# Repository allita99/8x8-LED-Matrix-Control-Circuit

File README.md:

# 8×8 LED Matrix Control Shield

This repository contains the hardware design files for an 8×8 LED matrix controller capable of driving 64 LEDs at 15 V. The design was created using KiCad and includes all necessary files for review, modification, and fabrication.

---

## Overview

- 8×8 LED matrix control (64 LEDs)
- Designed for 15 V LED operation
- Fully custom PCB layout
- Suitable for applications such as visual interfaces, experimental setups, or embedded systems

---

## Repository Contents

- **KiCad Project Files**  
  Schematic and PCB layout files for editing and further development.

- **Gerber Files**  
  Ready-to-manufacture files for PCB fabrication.

- **Images**  
  Rendered views and design previews of the board and schematics.

---

## PCB Render (Assembled View)

---

## Schematic

---

## PCB Layout

### Top Layer

### Bottom Layer

---

## Getting Started

1. Clone the repository:
   ```bash
   git clone <your-repo-url>

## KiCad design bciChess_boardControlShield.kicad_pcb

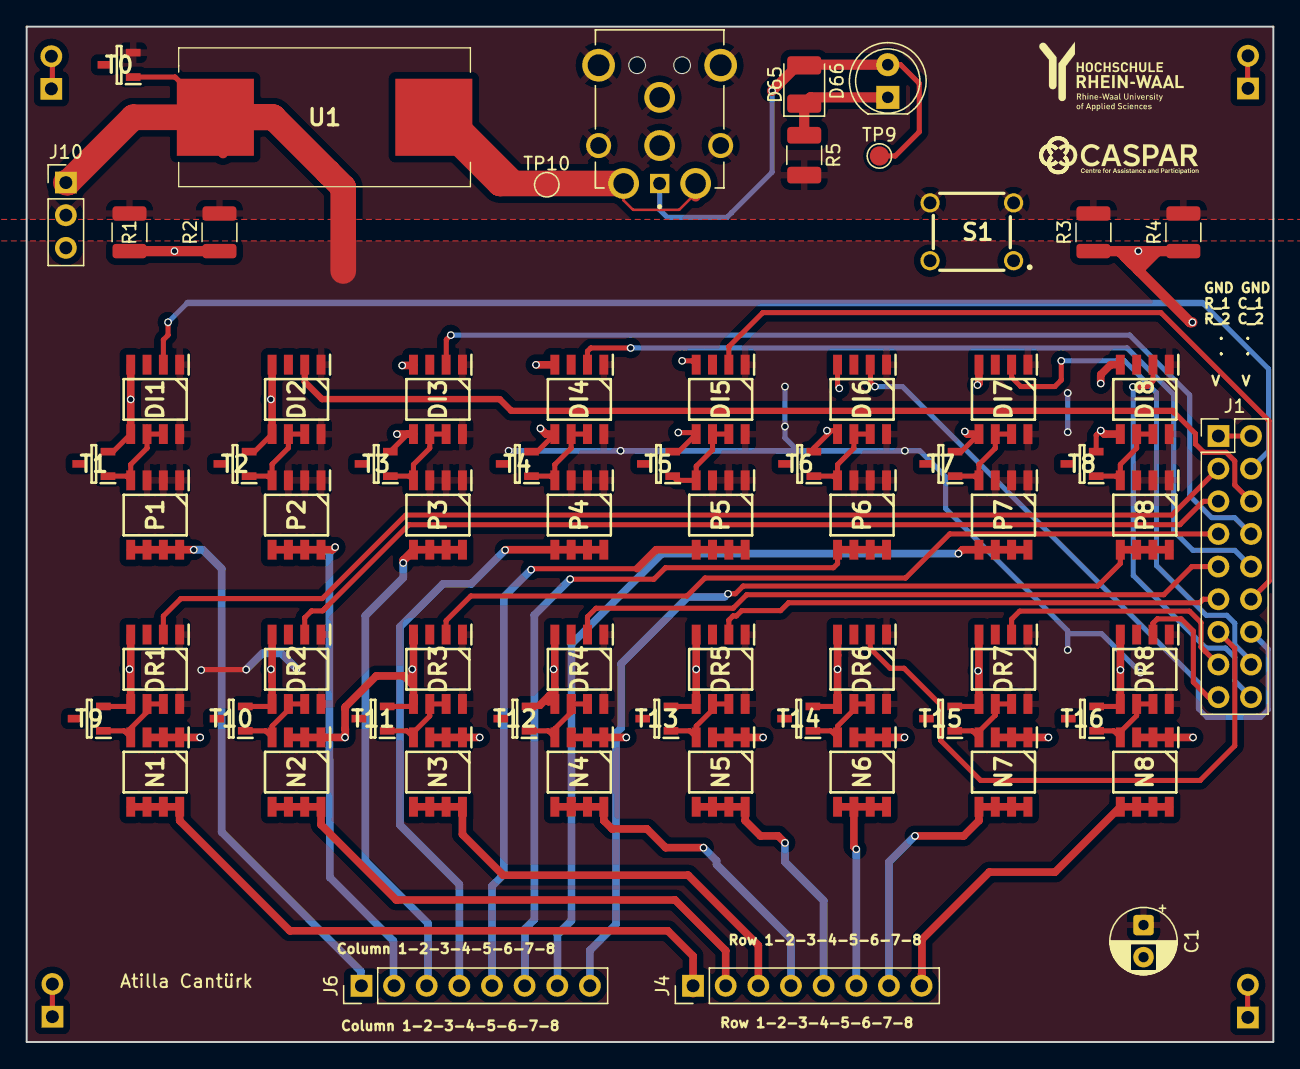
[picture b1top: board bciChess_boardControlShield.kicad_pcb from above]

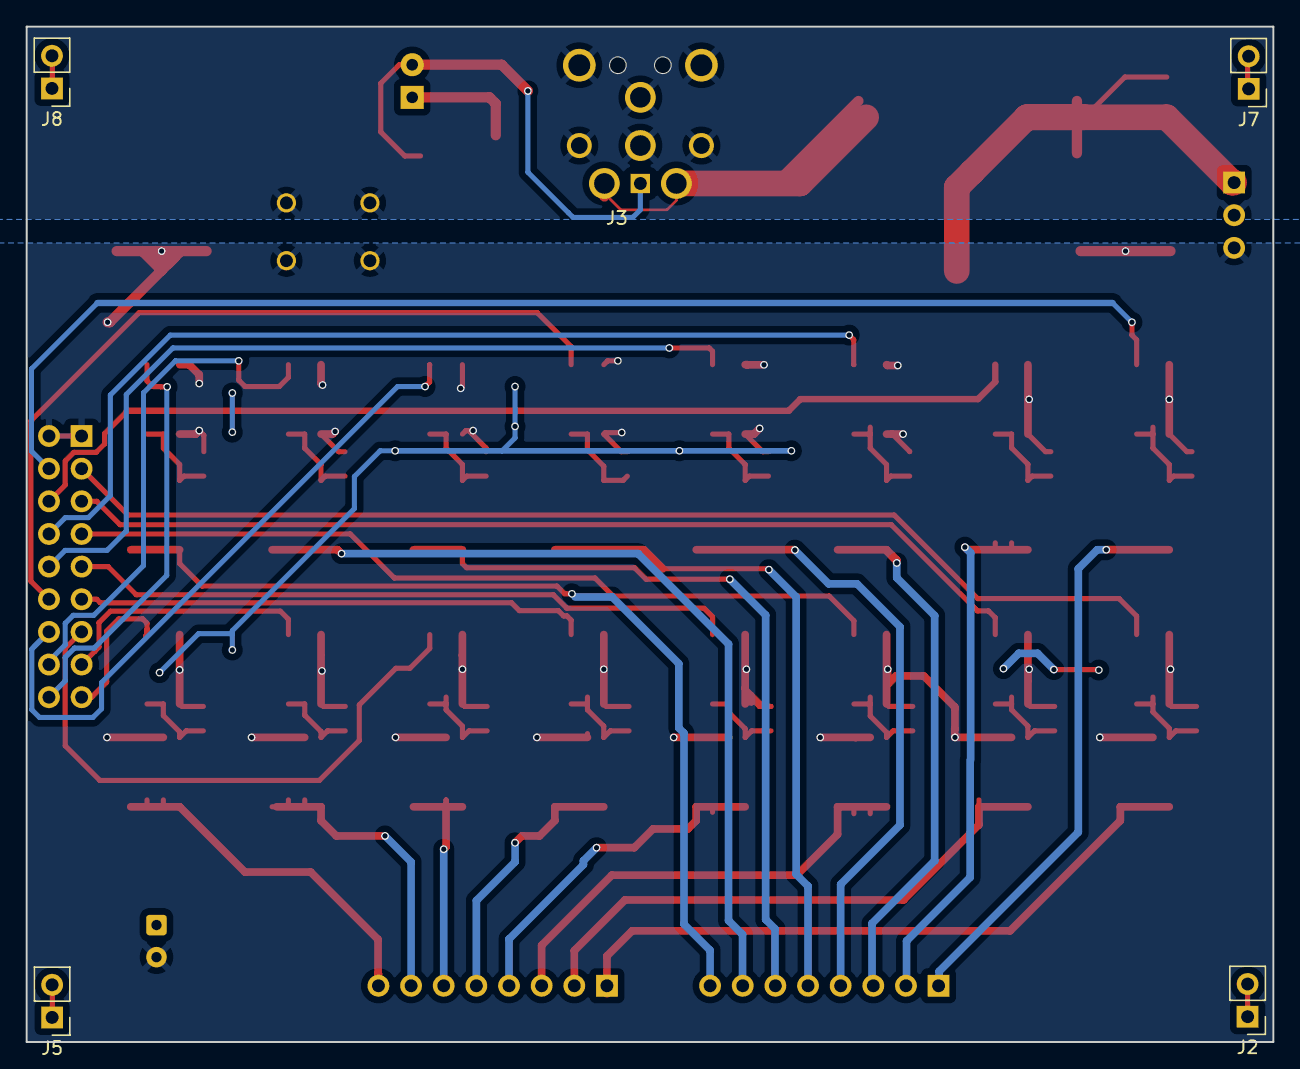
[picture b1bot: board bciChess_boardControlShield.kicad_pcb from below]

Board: 2 copper layers, 97.0 x 79.0 mm, 70 parts (4 on the bottom side), 58 nets.

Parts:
C1: C_Polarized; CP_Radial_D5.0mm_P2.50mm
D65: LED; LED_1210_3225Metric_Pad1.42x2.65mm_HandSolder
D66: LED; LED_D5.0mm
DI1, DI2, DI3, DI4, DI5, DI6, DI7, DI8: TC4429; SOIC127P600X175-8N
DR1, DR2, DR3, DR4, DR5, DR6, DR7, DR8: TC4420; SOIC127P600X175-8N
J1: Conn_02x09_Row_Letter_First; PinHeader_2x09_P2.54mm_Vertical
J2, J5, J7, J8: Conn_01x02_Pin; PinHeader_1x02_P2.54mm_Vertical
J3: PJ-096H; SAMESKY_PJ-096H
J4, J6: Screw_Terminal_01x08; PinHeader_1x08_P2.54mm_Vertical
J10: Conn_01x03_Pin; PinHeader_1x03_P2.54mm_Vertical
N1, N2, N3, N4, N5, N6, N7, N8: DMN3009SSS-13; SOIC127P600X175-8N
P1, P2, P3, P4, P5, P6, P7, P8: SI4101DY-T1-GE3; SOIC127P600X175-8N
R1, R2, R3, R4: R; R_1210_3225Metric
R5: R; R_1210_3225Metric_Pad1.30x2.65mm_HandSolder
S1: FSM2JH; FSM4JH
T0, T1, T2, T3, T4, T5, T6, T7, T8, T9, T10, T11, T12, T13, T14, T15, T16: ESD15VT2-TP; SOT95P237X125-3N
TP9, TP10: TestPoint; TestPoint_Pad_D1.5mm
U1: 0031.8221; 00318221

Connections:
Col_1: J6.1, P1.5 (D_1), P1.6 (D_2), P1.7 (D_3), P1.8 (D_4)
Col_1_fet: DI1.6 (OUTPUT_1), DI1.7 (OUTPUT_2), P1.4 (G), T1.1 (K1)
Col_2: J6.2, P2.5 (D_1), P2.6 (D_2), P2.7 (D_3), P2.8 (D_4)
Col_2_fet: DI2.6 (OUTPUT_1), DI2.7 (OUTPUT_2), P2.4 (G), T2.1 (K1)
Col_3: J6.3, P3.5 (D_1), P3.6 (D_2), P3.7 (D_3), P3.8 (D_4)
Col_3_fet: DI3.6 (OUTPUT_1), DI3.7 (OUTPUT_2), P3.4 (G), T3.1 (K1)
Col_4: J6.4, P4.5 (D_1), P4.6 (D_2), P4.7 (D_3), P4.8 (D_4)
Col_4_fet: DI4.6 (OUTPUT_1), DI4.7 (OUTPUT_2), P4.4 (G), T4.1 (K1)
Col_5: J6.5, P5.5 (D_1), P5.6 (D_2), P5.7 (D_3), P5.8 (D_4)
Col_5_fet: DI5.6 (OUTPUT_1), DI5.7 (OUTPUT_2), P5.4 (G), T5.1 (K1)
Col_6: J6.6, P6.5 (D_1), P6.6 (D_2), P6.7 (D_3), P6.8 (D_4)
Col_6_fet: DI6.6 (OUTPUT_1), DI6.7 (OUTPUT_2), P6.4 (G), T6.1 (K1)
Col_7: J6.7, P7.5 (D_1), P7.6 (D_2), P7.7 (D_3), P7.8 (D_4)
Col_7_fet: DI7.6 (OUTPUT_1), DI7.7 (OUTPUT_2), P7.4 (G), T7.1 (K1)
Col_8: J6.8, P8.5 (D_1), P8.6 (D_2), P8.7 (D_3), P8.8 (D_4)
Col_8_fet: DI8.6 (OUTPUT_1), DI8.7 (OUTPUT_2), P8.4 (G), T8.1 (K1)
GND2: J3.2_1, J3.2_2, J3.SH1 (SHIELD), J3.SH2 (SHIELD__1), J3.SH3 (SHIELD__2), J3.SH4 (SHIELD__3), J10.2, R1.2, R2.2, R3.2, R4.2, R5.2, S1.3, S1.4, T0.2 (K2)
unnamed: D65.2 (A), D66.2 (A), J3.1, TP9.1
unnamed: D65.1 (K), D66.1 (K), R5.1
unnamed: J2.1, J2.2
unnamed: J5.1, J5.2
unnamed: J7.1, J7.2
unnamed: J8.1, J8.2
Raw_Vcc: J3.3, J3.4, TP10.1, U1.1
Row_1: J4.1, N1.5 (D_1), N1.6 (D_2), N1.7 (D_3), N1.8 (D_4)
Row_1_fet: DR1.6 (OUTPUT_1), DR1.7 (OUTPUT_2), N1.4 (G), T9.1 (K1)
Row_2: J4.2, N2.5 (D_1), N2.6 (D_2), N2.7 (D_3), N2.8 (D_4)
Row_2_fet: DR2.6 (OUTPUT_1), DR2.7 (OUTPUT_2), N2.4 (G), T10.1 (K1)
Row_3: J4.3, N3.5 (D_1), N3.6 (D_2), N3.7 (D_3), N3.8 (D_4)
Row_3_fet: DR3.6 (OUTPUT_1), DR3.7 (OUTPUT_2), N3.4 (G), T11.1 (K1)
Row_4: J4.4, N4.5 (D_1), N4.6 (D_2), N4.7 (D_3), N4.8 (D_4)
Row_4_fet: DR4.6 (OUTPUT_1), DR4.7 (OUTPUT_2), N4.4 (G), T12.1 (K1)
Row_5: J4.5, N5.5 (D_1), N5.6 (D_2), N5.7 (D_3), N5.8 (D_4)
Row_5_fet: DR5.6 (OUTPUT_1), DR5.7 (OUTPUT_2), N5.4 (G), T13.1 (K1)
Row_6: J4.6, N6.5 (D_1), N6.6 (D_2), N6.7 (D_3), N6.8 (D_4)
Row_6_fet: DR6.6 (OUTPUT_1), DR6.7 (OUTPUT_2), N6.4 (G), T14.1 (K1)
Row_7: J4.7, N7.5 (D_1), N7.6 (D_2), N7.7 (D_3), N7.8 (D_4)
Row_7_fet: DR7.6 (OUTPUT_1), DR7.7 (OUTPUT_2), N7.4 (G), T15.1 (K1)
Row_8: J4.8, N8.5 (D_1), N8.6 (D_2), N8.7 (D_3), N8.8 (D_4)
Row_8_fet: DR8.6 (OUTPUT_1), DR8.7 (OUTPUT_2), N8.4 (G), T16.1 (K1)
VSS: C1.1, DI1.1 (VDD_1), DI1.8 (VDD_2), DI2.1 (VDD_1), DI2.8 (VDD_2), DI3.1 (VDD_1), DI3.8 (VDD_2), DI4.1 (VDD_1), DI4.8 (VDD_2), DI5.1 (VDD_1), DI5.8 (VDD_2), DI6.1 (VDD_1), DI6.8 (VDD_2), DI7.1 (VDD_1), DI7.8 (VDD_2), DI8.1 (VDD_1), DI8.8 (VDD_2), DR1.1 (VDD_1), DR1.8 (VDD_2), DR2.1 (VDD_1), DR2.8 (VDD_2), DR3.1 (VDD_1), DR3.8 (VDD_2), DR4.1 (VDD_1), DR4.8 (VDD_2), DR5.1 (VDD_1), DR5.8 (VDD_2), DR6.1 (VDD_1), DR6.8 (VDD_2), DR7.1 (VDD_1), DR7.8 (VDD_2), DR8.1 (VDD_1), DR8.8 (VDD_2), J10.1, P1.1 (S_1), P1.2 (S_2), P1.3 (S_3), P2.1 (S_1), P2.2 (S_2), P2.3 (S_3), P3.1 (S_1), P3.2 (S_2), P3.3 (S_3), P4.1 (S_1), P4.2 (S_2), P4.3 (S_3), P5.1 (S_1), P5.2 (S_2), P5.3 (S_3), P6.1 (S_1), P6.2 (S_2), P6.3 (S_3), P7.1 (S_1), P7.2 (S_2), P7.3 (S_3), P8.1 (S_1), P8.2 (S_2), P8.3 (S_3), T0.1 (K1), U1.2
µcC_1: DI1.2 (INPUT), J1.b2
µcC_2: DI2.2 (INPUT), J1.b3
µcC_3: DI3.2 (INPUT), J1.b4
µcC_4: DI4.2 (INPUT), J1.b5
µcC_5: DI5.2 (INPUT), J1.b6
µcC_6: DI6.2 (INPUT), J1.b7
µcC_7: DI7.2 (INPUT), J1.b8
µcC_8: DI8.2 (INPUT), J1.b9
µcC_GND: C1.2, DI1.4 (GND_1), DI1.5 (GND_2), DI2.4 (GND_1), DI2.5 (GND_2), DI3.4 (GND_1), DI3.5 (GND_2), DI4.4 (GND_1), DI4.5 (GND_2), DI5.4 (GND_1), DI5.5 (GND_2), DI6.4 (GND_1), DI6.5 (GND_2), DI7.4 (GND_1), DI7.5 (GND_2), DI8.4 (GND_1), DI8.5 (GND_2), DR1.4 (GND_1), DR1.5 (GND_2), DR2.4 (GND_1), DR2.5 (GND_2), DR3.4 (GND_1), DR3.5 (GND_2), DR4.4 (GND_1), DR4.5 (GND_2), DR5.4 (GND_1), DR5.5 (GND_2), DR6.4 (GND_1), DR6.5 (GND_2), DR7.4 (GND_1), DR7.5 (GND_2), DR8.4 (GND_1), DR8.5 (GND_2), J1.a1, J1.b1, J10.3, N1.1 (S_1), N1.2 (S_2), N1.3 (S_3), N2.1 (S_1), N2.2 (S_2), N2.3 (S_3), N3.1 (S_1), N3.2 (S_2), N3.3 (S_3), N4.1 (S_1), N4.2 (S_2), N4.3 (S_3), N5.1 (S_1), N5.2 (S_2), N5.3 (S_3), N6.1 (S_1), N6.2 (S_2), N6.3 (S_3), N7.1 (S_1), N7.2 (S_2), N7.3 (S_3), N8.1 (S_1), N8.2 (S_2), N8.3 (S_3), R1.1, R2.1, R3.1, R4.1, S1.1, S1.2, T1.2 (K2), T2.2 (K2), T3.2 (K2), T4.2 (K2), T5.2 (K2), T6.2 (K2), T7.2 (K2), T8.2 (K2), T9.2 (K2), T10.2 (K2), T11.2 (K2), T12.2 (K2), T13.2 (K2), T14.2 (K2), T15.2 (K2), T16.2 (K2)
µcR_1: DR1.2 (INPUT), J1.a2
µcR_2: DR2.2 (INPUT), J1.a3
µcR_3: DR3.2 (INPUT), J1.a4
µcR_4: DR4.2 (INPUT), J1.a5
µcR_5: DR5.2 (INPUT), J1.a6
µcR_6: DR6.2 (INPUT), J1.a7
µcR_7: DR7.2 (INPUT), J1.a8
µcR_8: DR8.2 (INPUT), J1.a9

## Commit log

2026-03-30 Initial push
2026-03-30 Schematic fixes.
2026-03-30 gerber files pushed
